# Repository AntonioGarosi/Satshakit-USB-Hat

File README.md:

# Satshakit USB Hat
*A fabbable USB shield for the SatshaKit*

**This project is at a really early stage, untested and unpolished. Tests and updates will be posted when done.**

|  |  |
|-----|-----|

For further information regarding Satshakit, visit [its official repository](https://github.com/satshakit/satshakit).

For any enquiry, just [mail me](mailto:antonio_garosi@yahoo.it).

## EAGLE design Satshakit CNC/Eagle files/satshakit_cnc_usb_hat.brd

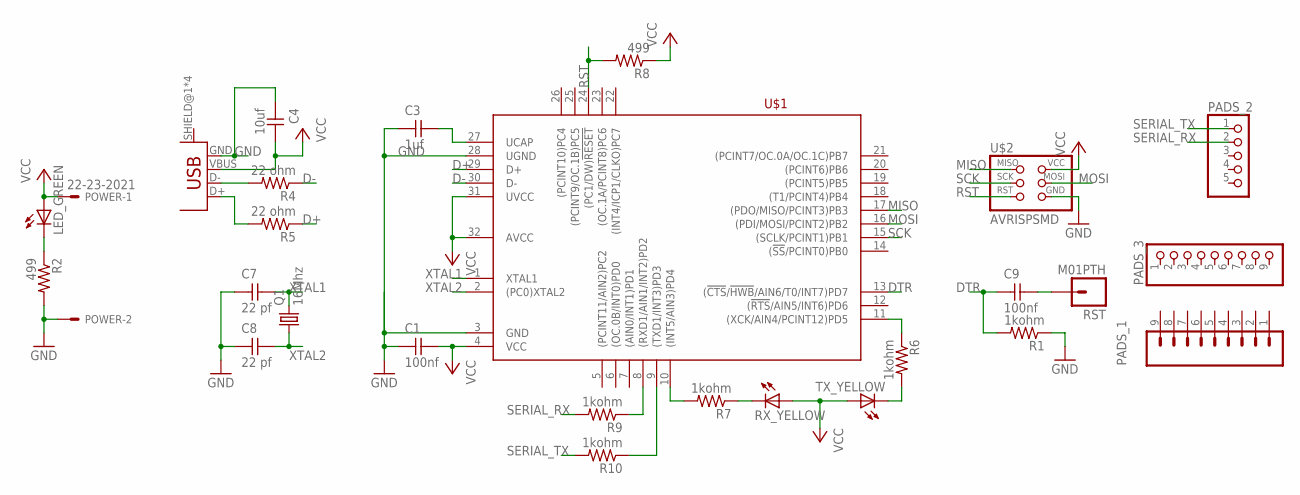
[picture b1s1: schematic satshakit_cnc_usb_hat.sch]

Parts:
C1, C9: 100nf; C1206FAB
C3: 1uf; C1206FAB
C4: 10uf; C1206FAB
C7, C8: 22 pf; C1206FAB
LED_GREEN: LED1206; 1206
PADS_1: M09LONGPADS; 1X09_LONGPADS
PADS_2: PINHD-1X5; 1X05
PADS_3: PINHD-1X9; 1X09
POWER: 22-23-2021
Q1: 16Mhz; CSM-7X-DU
R1, R6, R7, R9, R10: 1kohm; 1206
R2, R8: 499; 1206
R4, R5: 22 ohm; 1206
RST: M01PTH; 1X01
RX_YELLOW: LED1206; 1206
TX_YELLOW: LED1206; 1206
U$1: ATMEGA16U2-TQ; TQFP32-08THIN
U$2: AVRISPSMD; 2X03SMD
U$3: USB_MINIB

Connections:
D+: R5.1, U$1.29 (D+)
D-: R4.1, U$1.30 (D-)
DTR: C9.1, R1.2, U$1.13 ((!CTS!/!HWB!/AIN6/T0/INT7)PD7)
GND: C1.1, C3.1, C4.1, C7.1, C8.1, POWER.2, R1.1, R2.2, U$1.3 (GND), U$1.28 (UGND), U$2.6 (GND), U$3.GND
MISO: U$1.17 ((PDO/MISO/PCINT3)PB3), U$2.1 (MISO)
MOSI: U$1.16 ((PDI/MOSI/PCINT2)PB2), U$2.4 (MOSI)
unnamed: R6.2, TX_YELLOW.2 (C)
unnamed: R6.1, U$1.11 ((XCK/AIN4/PCINT12)PD5)
unnamed: R4.2, U$3.D-
unnamed: R5.2, U$3.D+
unnamed: C3.2, U$1.27 (UCAP)
unnamed: R7.2, U$1.10 ((INT5/AIN3)PD4)
unnamed: C9.2, RST.1
unnamed: R9.1, U$1.8 ((RXD1/AIN1/INT2)PD2)
unnamed: R7.1, RX_YELLOW.2 (C)
unnamed: R10.1, U$1.9 ((TXD1/INT3)PD3)
unnamed: LED_GREEN.2 (C), R2.1
RST: R8.2, U$1.24 ((PC1/DW)!RESET), U$2.5 (RST)
SCK: U$1.15 ((SCLK/PCINT1)PB1), U$2.3 (SCK)
SERIAL_RX: PADS_2.2, R9.2
SERIAL_TX: PADS_2.1, R10.2
VCC: C1.2, C4.2, LED_GREEN.1 (A), POWER.1, R8.1, RX_YELLOW.1 (A), TX_YELLOW.1 (A), U$1.4 (VCC), U$1.31 (UVCC), U$1.32 (AVCC), U$2.2 (VCC), U$3.VBUS
XTAL1: C7.2, Q1.2, U$1.1 (XTAL1)
XTAL2: C8.2, Q1.1, U$1.2 ((PC0)XTAL2)

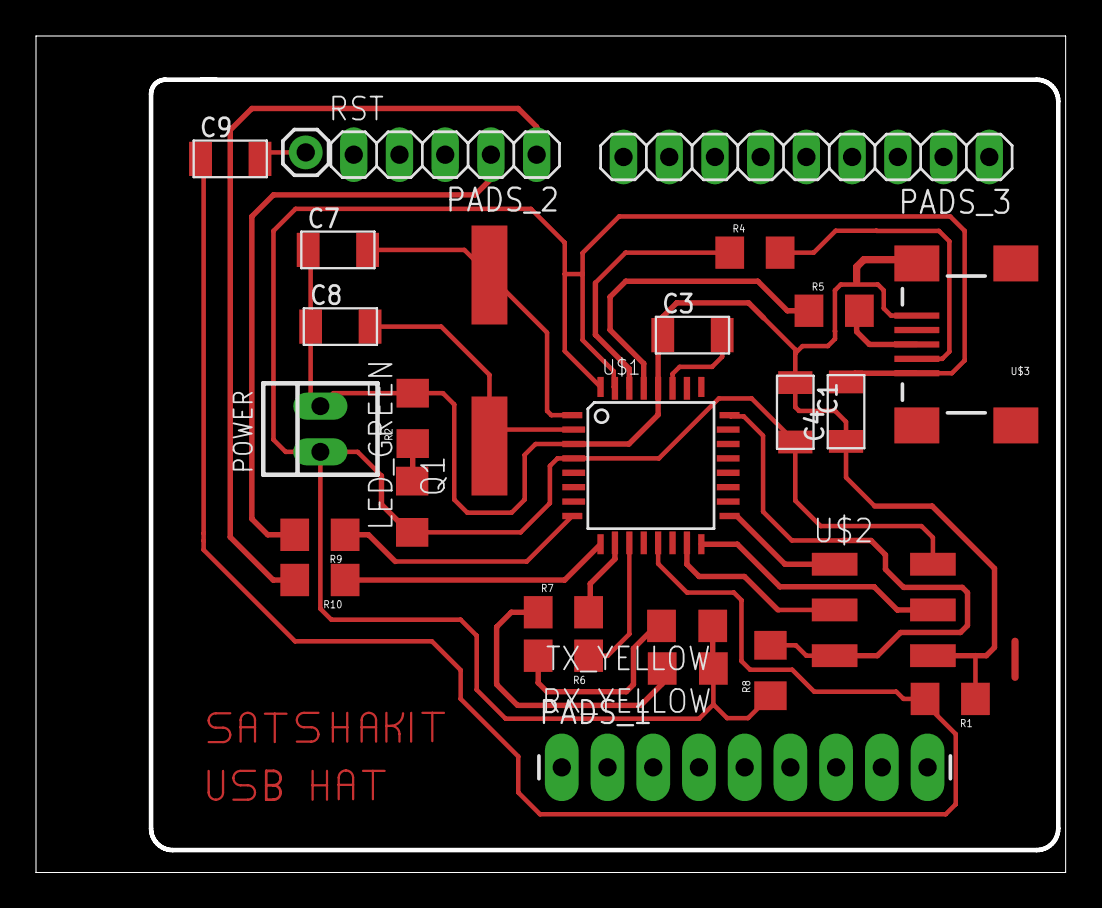
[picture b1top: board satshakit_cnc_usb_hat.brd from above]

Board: 2 copper layers, 56.9 x 46.2 mm, 27 parts (0 on the bottom side), 24 nets.

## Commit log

2018-08-09 Create LICENCE
2018-08-09 First drafts
2018-08-09 Add ignore
2018-08-19 New improved, simplified - yet to be properly testest - design. Most importantly it features a proper crystal trace and some elements redistribution
2018-08-25 Updated board. Reduced components and optimized traces. Added fancy writing
2018-08-25 Fixed img
2018-10-06 Board components and traces optimizations. Images still to update
2018-10-17 Made a bit of order

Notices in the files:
parts and their libraries:
01_SparkFun: Licensing: CC v3.0 Share-Alike You are welcome to use this library for commercial purposes.
